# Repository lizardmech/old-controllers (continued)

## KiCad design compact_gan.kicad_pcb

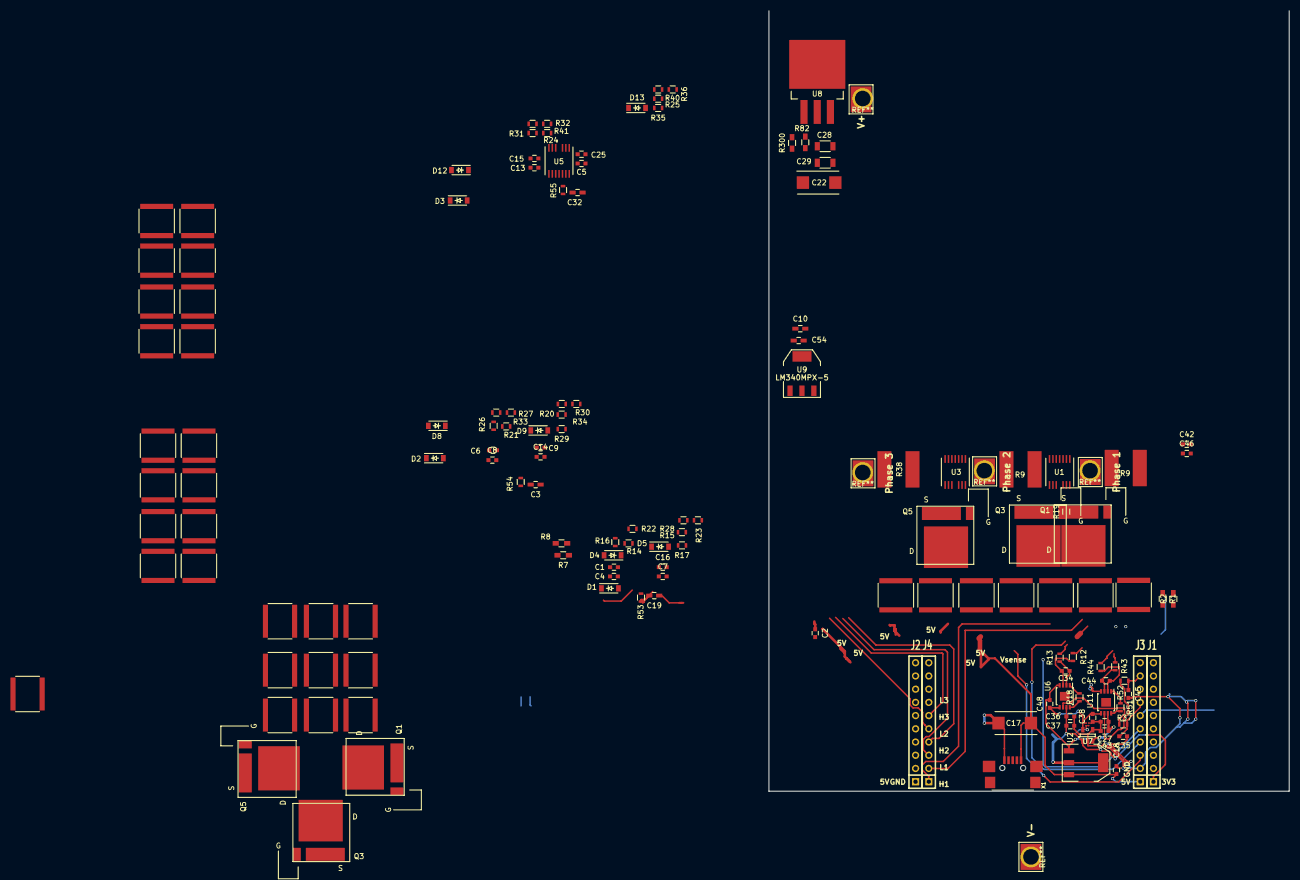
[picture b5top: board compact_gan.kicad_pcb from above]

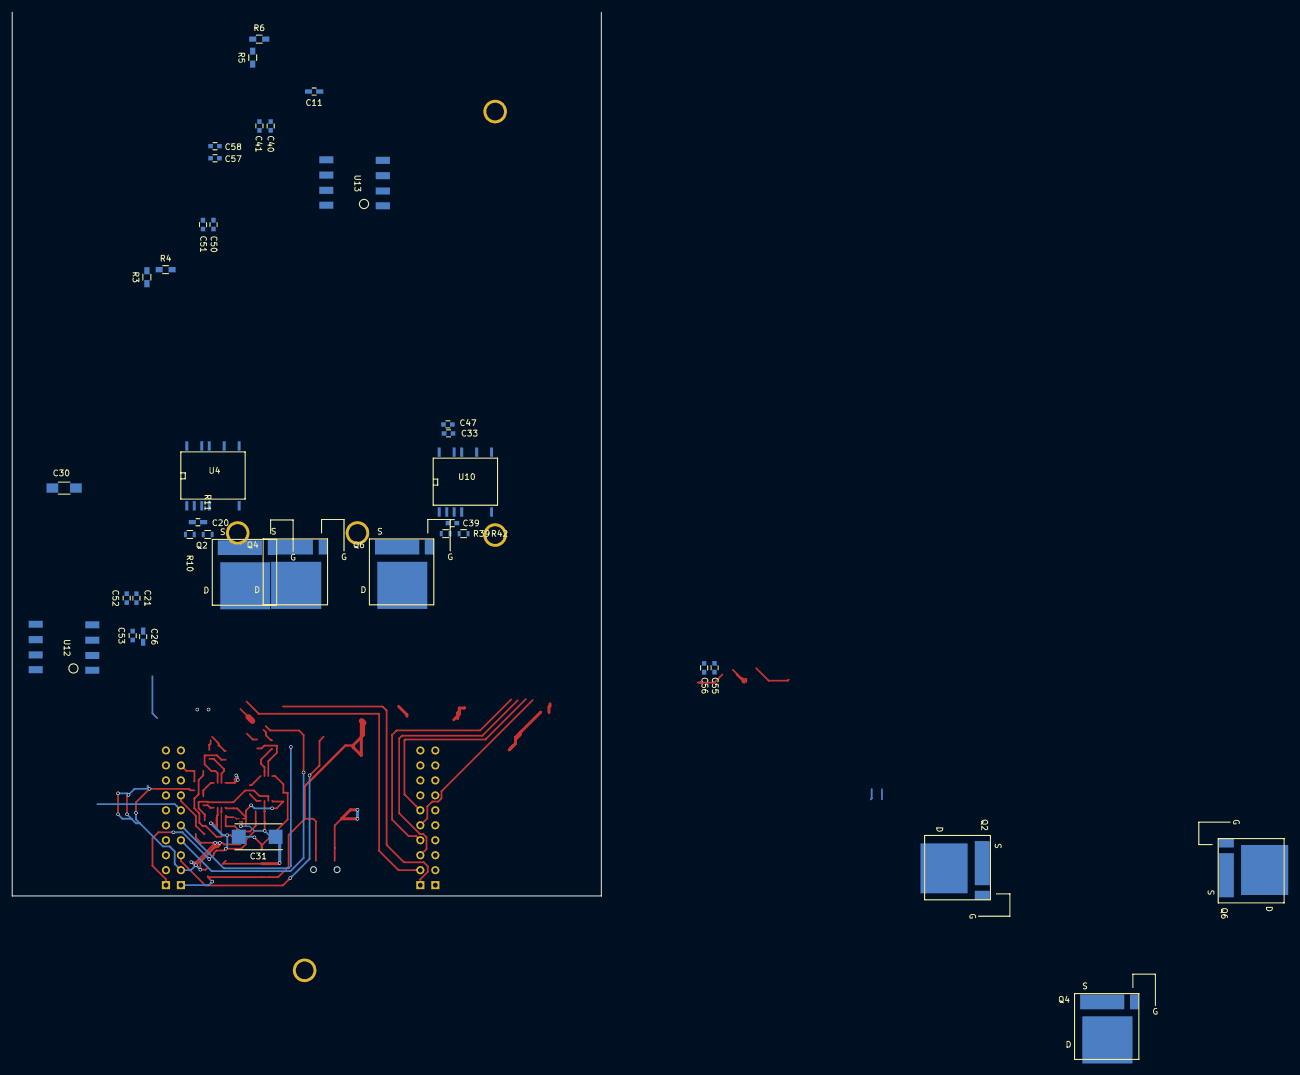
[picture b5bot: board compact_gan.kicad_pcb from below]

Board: 4 copper layers, 100.0 x 150.0 mm, 183 parts (37 on the bottom side), 74 nets.

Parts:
C1, C2, C6, C7, C13, C14, C25, C33, C36, C38, C41, C43, C46, C48, C50, C53, C55, C58: 0.1uf; C_0603
C3, C10, C19, C26, C32: 0.1uf; C_0603_HandSoldering
C4, C16: 2.2uf; C_0603
C5, C8, C9, C15: 2.2; C_0603
C11: 1uf; C_0603_HandSoldering
C17, C22, C31: 100uf; TantalC_SizeD_EIA-7343_Reflow
C18, C21, C27, C37, C40, C42, C47, C51, C52, C56, C57: 10uf; C_0603
C20: 33nf; C_0603_HandSoldering
C28, C29: 10uf; C_1206
C30: 2.2uf; C_1206_HandSoldering
C34, C44: 4.7nf; C_0603
C35, C45: 100pf; C_0603
C39: 33nf; C_0603
C49, C49#2, C49#3, C49#4, C49#5, C49#6, C49#7, C49#8, C49#9, C49#10, C49#11, C49#12, C49#13, C49#14, C49#15, C49#16, C49#17, C49#18, C49#19, C49#20, C49#21, C49#22, C49#23, C49#24, C49#25, C49#26, C49#27, C49#28, C49#29, C49#30, C49#31, C49#32, C49#33: 15uf; C_2225_invis
C54: 10uf; C_0603_HandSoldering
D1, D2, D3: DFLS1150-7; SOD-123
D4, D5, D8, D9, D12, D13: D_Schottky_Small; SOD-123
J1: Ti_Booster_40_J1; SIL-10J1
J2: Ti_Booster_40_J2; SIL-10J2
J3: Ti_Booster_40_J3; SIL-10J3
J4: Ti_Booster_40_J4; SIL-10J4
Phase 1: MOTOR3; 1PAD_4x5mm
Phase 2: MOTOR2; 1PAD_4x5mm
Phase 3: MOTOR1; 1PAD_4x5mm
Q1, Q1#2, Q2, Q2#2, Q3, Q3#2, Q4, Q4#2, Q5, Q5#2, Q6, Q6#2: FDMT-800; P-PG-HSOF-08
R1, R3, R5, R7: 1.3K; R_0603_HandSoldering
R2, R4, R6, R8: 39K; R_0603_HandSoldering
R9, R9#2, R38: 0.001R; shunt_ERJ-MS6SF1M0U
R10, R11, R37, R39, R42, R52: 20R; R_0603
R12, R13, R43, R44: R20; R_0603
R14, R15, R20, R21, R24, R25: 10R; R_0603
R16, R17, R26, R29, R31, R35: R4; R_0603
R18, R51: 10Mr; R_0603
R19, R28, R33, R34, R40, R41: ferrite; R_0603
R22, R23, R27, R30, R32, R36: R39k; R_0603
R53, R54, R55: r20; R_0603
R82: R; R_0603_HandSoldering
R300: R_Small; R_0603_HandSoldering
U1, U3, U5: ADuM7223; LGA-13
U2: TPS72116DBVR; SOT-23-5
U4, U10: SI8920; SI_8920SO-16
U6, U11: ad623; MSOP-8-1EP_3x3mm_Pitch0.65mm
U7: NCP1117ST33T3G; SOT-223
U8: tl783; TO-263-3Lead
U9: LM340MPX-5; SOT223_bcp53
U12, U13: R1SE-0505-R; recom_power
V+: IN+; 1PAD_4x5mm
V-: IN-; 1PAD_4x5mm
X1: MINI-USB-SCHIELD-32005-201; USB-UX60R-MB-5ST

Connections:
+1V5: C38.1, C48.1, U2.5, U6.5, U11.5
+3V3: C11.1, C27.1, C30.1, C31.1, C33.1, C36.1, C37.1, C42.1, C43.1, C46.1, C47.1, J1.1, U2.1, U2.3, U4.8, U6.7, U7.2, U10.8, U11.7
+5V: C3.2, C10.2, C17.1, C18.1, C19.2, C32.1, C50.2, C51.2, C54.1, C55.2, C56.2, J3.1, R53.2, R54.2, R55.2, U1.7, U3.7, U5.7, U7.3, U9.3, U12.2, U13.2, X1.1
+5VA: C21.1, C26.1, C52.2, C53.2, U4.1, U12.5
+5VD: C40.1, C41.1, C57.2, C58.2, U10.1, U13.5
/Power MOSFETS/CurrentA: C35.1, J3.7, R37.1
/Power MOSFETS/CurrentC: C45.1, J3.9, R52.1
/Power MOSFETS/H2_VS: C6.2, C8.2, Phase 2.1, Q3.2, Q3#2.2, Q4.1, Q4#2.1, R4.2, R27.1, U3.11
/Power MOSFETS/M_H1: J4.1, U1.2
/Power MOSFETS/M_H2: J4.3, U3.2
/Power MOSFETS/M_H3: J4.5, U5.2
/Power MOSFETS/M_L1: J4.2, U1.3
/Power MOSFETS/M_L2: J4.4, U3.3
/Power MOSFETS/M_L3: J4.6, U5.3
/Power MOSFETS/PHASE_1: Phase 1.1, R9.1, R9#2.1, R11.2
/Power MOSFETS/PHASE_3: Phase 3.1, R38.1, R42.2
/Power MOSFETS/sense1_N: R13.2, U4.6
/Power MOSFETS/sense1_P: R12.2, U4.7
/Power MOSFETS/sense2_N: R44.2, U10.6
/Power MOSFETS/sense2_P: R43.2, U10.7
GND: C2.2, C3.1, C5.2, C7.2, C9.2, C10.1, C11.2, C14.2, C16.2, C17.2, C18.2, C19.1, C22.2, C25.2, C27.2, C28.1, C29.1, C30.2, C31.2, C32.2, C33.2, C35.2, C36.2, C37.2, C38.2, C42.2, C43.2, C45.2, C46.2, C47.2, C48.2, C49.2, C49#2.2, C49#3.2, C49#4.2, C49#5.2, C49#6.2, C49#7.2, C49#8.2, C49#9.2, C49#10.2, C49#11.2, C49#12.2, C49#13.2, C49#14.2, C49#15.2, C49#16.2, C49#17.2, C49#18.2, C49#19.2, C49#20.2, C49#21.2, C49#22.2, C49#23.2, C49#24.2, C49#25.2, C49#26.2, C49#27.2, C49#28.2, C49#29.2, C49#30.2, C49#31.2, C49#32.2, C49#33.2, C50.1, C51.1, C54.2, C55.1, C56.1, J2.1, J3.2, Q2.2, Q2#2.2, Q4.2, Q4#2.2, Q6.2, Q6#2.2, R1.1, R3.1, R5.1, R7.1, R23.1, R30.1, R36.1, R300.2, U1.1, U1.4, U1.8, U2.2, U2.4, U3.1, U3.4, U3.8, U4.5, U5.1, U5.4, U5.8, U6.4, U7.1, U9.2, U10.5, U11.4, U12.1, U13.1, V-.1, X1.5
GNDA: C1.2, C4.2, C21.2, C26.2, C52.1, C53.1, Q1.2, Q1#2.2, Q2.1, Q2#2.1, R2.2, R9.2, R9#2.2, R10.2, R22.1, U1.11, U4.4, U12.4
GNDD: C13.2, C15.2, C40.2, C41.2, C57.1, C58.1, Q5.2, Q5#2.2, Q6.1, Q6#2.1, R6.2, R32.1, R38.2, R39.2, U5.11, U10.4, U13.4
unnamed: C1.1, C4.1, D1.1, U1.13
unnamed: C6.1, C8.1, D2.1, U3.13
unnamed: C13.1, C15.1, D3.1, U5.13
unnamed: C20.1, R10.1, U4.2
unnamed: C20.2, R11.1, U4.3
unnamed: C34.1, R12.1, U6.3
unnamed: C34.2, R13.1, U6.2
unnamed: C39.1, R39.1, U10.2
unnamed: C39.2, R42.1, U10.3
unnamed: C44.1, R43.1, U11.3
unnamed: C44.2, R44.1, U11.2
unnamed: D4.1, R14.2, U1.12
unnamed: D4.2, R16.2
unnamed: D5.1, R15.1, U1.9
unnamed: D5.2, R17.2
unnamed: D8.1, R21.1, U3.12
unnamed: D8.2, R26.2
unnamed: D9.1, R20.1, U3.9
unnamed: D9.2, R29.2
unnamed: D12.1, R24.1, U5.12
unnamed: D12.2, R31.2
unnamed: D13.1, R25.1, U5.9
unnamed: D13.2, R35.2
unnamed: J3.3, R7.2, R8.1
unnamed: J3.4, R1.2, R2.1
unnamed: J3.5, R3.2, R4.1
unnamed: J3.6, R5.2, R6.1
unnamed: Q1.3, Q1#2.3, R19.1
unnamed: Q2.3, Q2#2.3, R28.2
unnamed: Q3.3, Q3#2.3, R33.1
unnamed: Q4.3, Q4#2.3, R34.1
unnamed: Q5.3, Q5#2.3, R41.1
unnamed: Q6.3, Q6#2.3, R40.1
unnamed: R14.1, R16.1, R19.2, R22.2
unnamed: R15.2, R17.1, R23.2, R28.1
unnamed: R18.1, U6.8
unnamed: R18.2, U6.1
unnamed: R20.2, R29.1, R30.2, R34.2
unnamed: R21.2, R26.1, R27.2, R33.2
unnamed: R24.2, R31.1, R32.2, R41.2
unnamed: R25.2, R35.1, R36.2, R40.2
unnamed: R37.2, U6.6
unnamed: R51.1, U11.8
unnamed: R51.2, U11.1
unnamed: R52.2, U11.6
unnamed: R53.1, U1.5
unnamed: R54.1, U3.5
unnamed: R55.1, U5.5
unnamed: R82.2, R300.1, U8.1
VDD: C2.1, C5.1, C7.1, C9.1, C14.1, C16.1, C22.1, C25.1, C28.2, C29.2, D1.2, D2.2, D3.2, R82.1, U1.10, U3.10, U5.10, U8.2, U8.4, U9.1
V_SUPPLY: C49.1, C49#2.1, C49#3.1, C49#4.1, C49#5.1, C49#6.1, C49#7.1, C49#8.1, C49#9.1, C49#10.1, C49#11.1, C49#12.1, C49#13.1, C49#14.1, C49#15.1, C49#16.1, C49#17.1, C49#18.1, C49#19.1, C49#20.1, C49#21.1, C49#22.1, C49#23.1, C49#24.1, C49#25.1, C49#26.1, C49#27.1, C49#28.1, C49#29.1, C49#30.1, C49#31.1, C49#32.1, C49#33.1, Q1.1, Q1#2.1, Q3.1, Q3#2.1, Q5.1, Q5#2.1, R8.2, U8.3, V+.1
